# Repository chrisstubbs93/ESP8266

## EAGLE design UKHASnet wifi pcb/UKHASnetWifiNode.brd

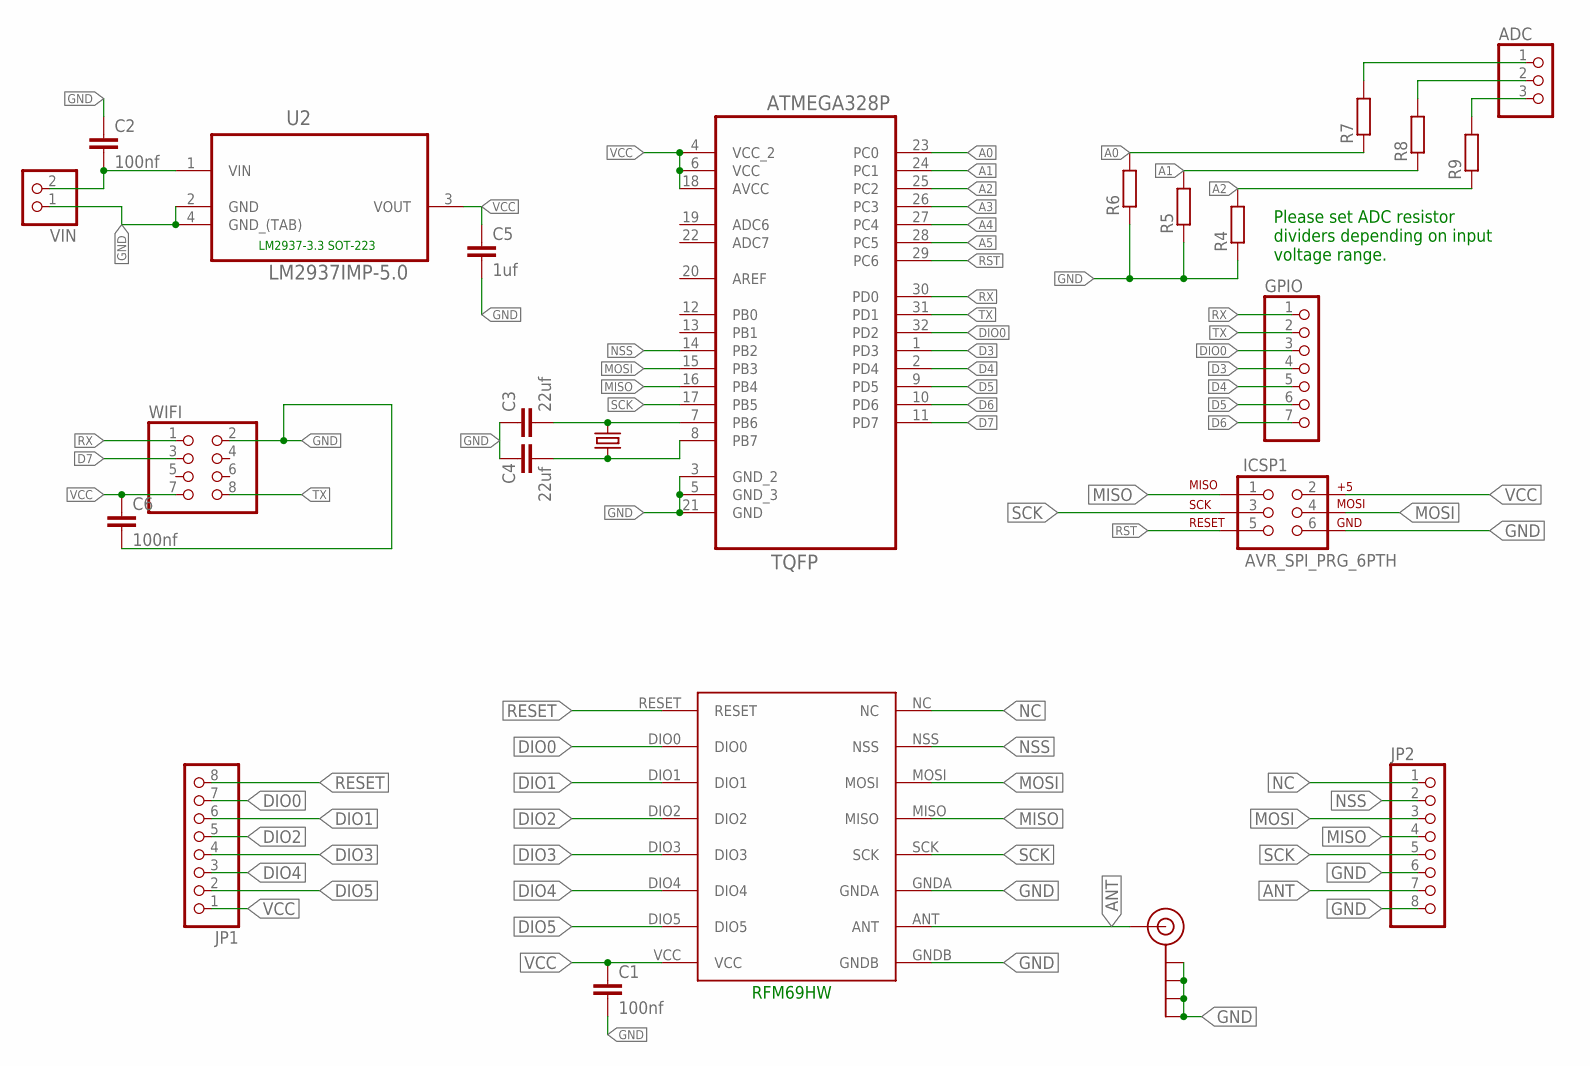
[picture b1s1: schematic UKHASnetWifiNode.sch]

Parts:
ADC: PINHD-1X3; 1X03
C1, C2, C6: 100nf; C0603
C3, C4: 22uf; C0603
C5: 1uf; C0603
GPIO: PINHD-1X7; 1X07
ICSP1: AVR_SPI_PRG_6PTH; 2X3
J$1: SMA_EDGE; SMA-EDGE
JP1, JP2: PINHD-1X8; 1X08
R4, R5, R6, R7, R8, R9: R-EU_R0603; R0603
U1: ATMEGA328P-AU; QFP80P900X900X120-32N
U2: LM2937IMP-5.0; SOT230P700X180-4N
U$1: RFM69HW; RFM
U$2: 8MHz; ABM03_HC49
VIN: PINHD-1X2; 1X02
WIFI: PINHD-2X4; 2X04

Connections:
A0: R6.2, R7.1, U1.23 (PC0)
A1: R5.2, R8.1, U1.24 (PC1)
A2: R4.2, R9.1, U1.25 (PC2)
A3: U1.26 (PC3)
A4: U1.27 (PC4)
A5: U1.28 (PC5)
ANT: J$1.SIG (SIGNAL), JP2.7, U$1.ANT
D3: GPIO.4, U1.1 (PD3)
D4: GPIO.5, U1.2 (PD4)
D5: GPIO.6, U1.9 (PD5)
D6: GPIO.7, U1.10 (PD6)
D7: U1.11 (PD7), WIFI.3 (CH_PD)
DIO0: GPIO.3, JP1.7, U1.32 (PD2), U$1.DIO0
DIO1: JP1.6, U$1.DIO1
DIO2: JP1.5, U$1.DIO2
DIO3: JP1.4, U$1.DIO3
DIO4: JP1.3, U$1.DIO4
DIO5: JP1.2, U$1.DIO5
GND: C1.2, C2.1, C3.1, C4.1, C5.2, C6.2, ICSP1.6, J$1.GND@0 (GND), J$1.GND@1 (GND), J$1.GND@2 (GND), J$1.GND@3 (GND), JP2.6, JP2.8, R4.1, R5.1, R6.1, U1.3 (GND_2), U1.5 (GND_3), U1.21 (GND), U2.2 (GND), U2.4 (GND_(TAB)), U$1.GNDA, U$1.GNDB, VIN.1, WIFI.2 (GND)
MISO: ICSP1.1, JP2.4, U1.16 (PB4), U$1.MISO
MOSI: ICSP1.4, JP2.3, U1.15 (PB3), U$1.MOSI
unnamed: C3.2, U1.7 (PB6), U$2.2
unnamed: C4.2, U1.8 (PB7), U$2.1
unnamed: C2.2, U2.1 (VIN), VIN.2
unnamed: ADC.1, R7.2
unnamed: ADC.2, R8.2
unnamed: ADC.3, R9.2
NC: JP2.1, U$1.NC
NSS: JP2.2, U1.14 (PB2), U$1.NSS
RESET: JP1.8, U$1.RESET
RST: ICSP1.5, U1.29 (PC6)
RX: GPIO.1, U1.30 (PD0), WIFI.1 (TXD)
SCK: ICSP1.3, JP2.5, U1.17 (PB5), U$1.SCK
TX: GPIO.2, U1.31 (PD1), WIFI.8 (RXD)
VCC: C1.1, C5.1, C6.1, ICSP1.2, JP1.1, U1.4 (VCC_2), U1.6 (VCC), U1.18 (AVCC), U2.3 (VOUT), U$1.VCC, WIFI.7 (VCC)

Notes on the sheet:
LM2937-3.3 SOT-223
Please set ADC resistor dividers depending on input voltage range.
RFM69HW

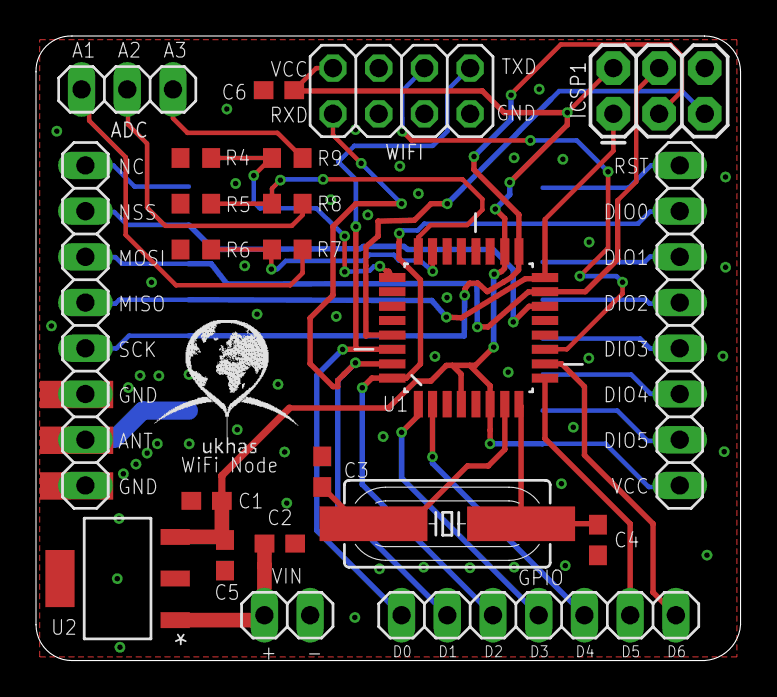
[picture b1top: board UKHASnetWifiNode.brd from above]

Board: 2 copper layers, 39.1 x 34.7 mm, 24 parts (1 on the bottom side), 32 nets.

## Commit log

2014-11-01 Initial commit
    It all pretty much works, and is fairly commented
2014-11-01 Packet as upload param
    Actually have the upload function take the packet as a parameter
2014-11-02 PCB files and Phil's repeater code added
    EAGLE pcb files and hacky solution to add wifi uploads to Phil's
    repeater code. This is by no means complete but is working and seems
    stable after 24 hours.
2014-11-02 Schematic tidied
2014-11-09 Upload after RX not TX now, RSSI added.
    The code used to upload just before TX'ing a repeated packet, meaning it
    missed packets with a TTL of 0. Packets are now uploaded straight after
    they are RX'd.
    RSSI is also now uploaded.
2014-11-09 Added status LEDs
2020-04-04 Create UKHASnetWifiNode.pdf
    added circuit PDF

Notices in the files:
parts and their libraries:
SparkFun-Connectors: Licensing: CC v3.0 Share-Alike You are welcome to use this library for commercial purposes.
